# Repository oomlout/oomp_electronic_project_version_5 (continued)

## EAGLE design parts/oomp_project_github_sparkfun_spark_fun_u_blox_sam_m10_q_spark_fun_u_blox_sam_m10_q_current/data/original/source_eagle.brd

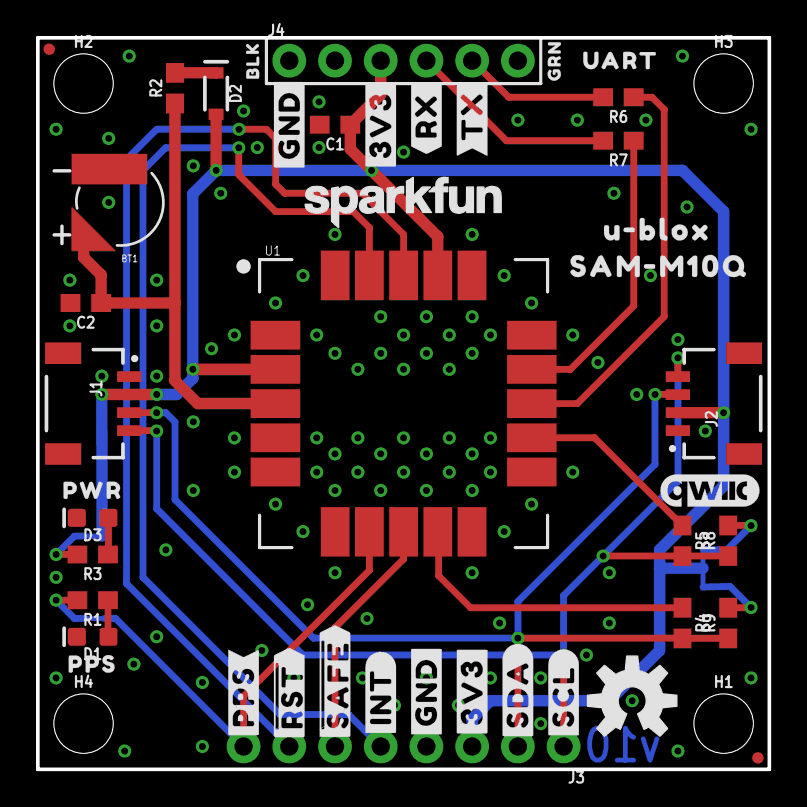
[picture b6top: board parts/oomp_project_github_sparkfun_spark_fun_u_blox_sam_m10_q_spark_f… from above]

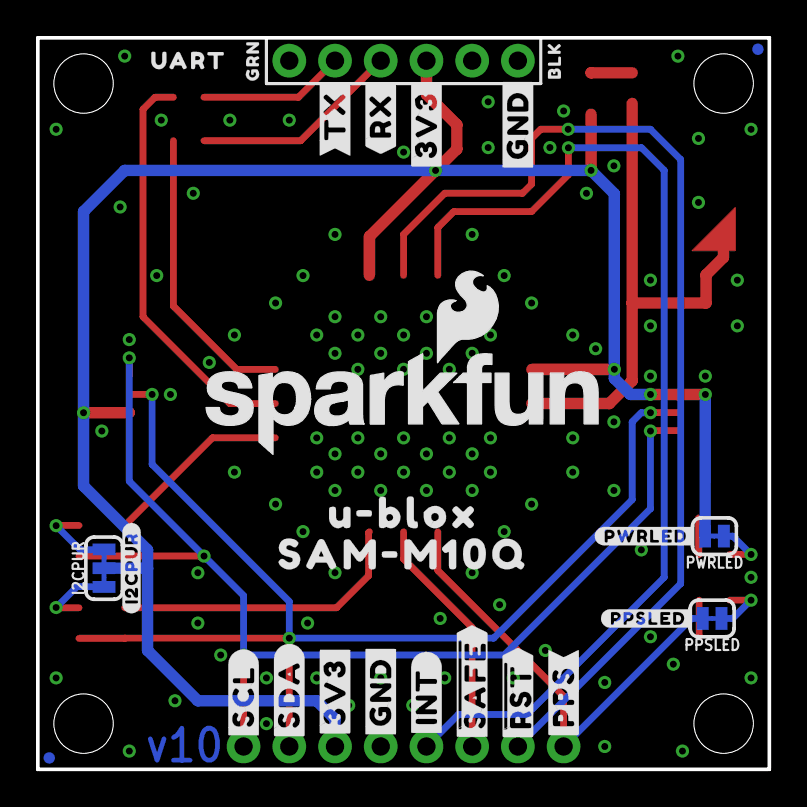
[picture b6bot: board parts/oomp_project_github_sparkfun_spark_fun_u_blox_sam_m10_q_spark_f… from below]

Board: 2 copper layers, 40.6 x 40.6 mm, 76 parts (26 on the bottom side), 22 nets.

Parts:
BT1: 6.8MM_COIN_CELL; MS421R_IV03E
C1, C2: 0.1uF; 0603
D1: Yellow; LED-0603
D2: 0.5A/40V/420mV; SOD-323
D3: RED; LED-0603
FD1, FD2, FD3, FD4: FIDUCIALUFIDUCIAL; FIDUCIAL-MICRO
FRAME1: FRAME-LETTER; CREATIVE_COMMONS
H1, H2, H3, H4: STAND-OFF
I2CPUR: JUMPER-SMT_3_2-NC_TRACE_SILK; SMT-JUMPER_3_2-NC_TRACE_SILK
J1, J2: Qwiic Right Angle; JST04_1MM_RA
J3: 1X08_NO_SILK
J4: BOOT; 1X06_NO_SILK
LOGO1: OSHW-LOGOM; OSHW-LOGO-M
LOGO2: SFE_LOGO_NAME_FLAME.2_INCH; SFE_LOGO_NAME_FLAME_.2
LOGO3: QWIIC_LOGO_CONNECTOR; QWIIC_5.5MM
PPSLED: JUMPER-SMT_2_NC_TRACE_SILK; SMT-JUMPER_2_NC_TRACE_SILK
PWRLED: JUMPER-SMT_2_NC_TRACE_SILK; SMT-JUMPER_2_NC_TRACE_SILK
R1, R8, R9: 2.2k; 0603
R2: 3.3k; 0603
R3: 1k; 0603
R4, R5: 22Ω; 0603
R6, R7: 470; 0603
U1: U-BLOX_SAM_M10Q-00B_100_PASTE; SAM-M10Q_100PASTE
U$1: SFE_LOGO_FLAME_STOP_.1
U$2: SAM#M10Q11
U$3, U$4: BLK4
U$5, U$6: GRN5
U$7, U$8: UART7
U$9: PPS9
U$10: PWR10
U$11, U$12: #TX#12
U$13, U$14: #RX#13
U$15, U$16, U$22, U$23: #3V3#0
U$17, U$20: #GND#4
U$18: U#BLOX11
U$19, U$21: #GND#5
U$24, U$25: #SCL#6
U$26, U$27: #SDA#7
U$28, U$29: #INT#8
U$30, U$33: ##RST##15
U$31: SFE_LOGO_NAME_.1
U$32: SAM#M10Q12
U$34, U$35: #PPS#13
U$36, U$37: ##SAFE##16
U$38: U#BLOX12
U$40: #PPSLED#0
U$41: #I2CPUR#0
U$42: #PWRLED#0

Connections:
3.3V: C1.1, D2.A, I2CPUR.2, J1.2, J2.2, J3.3, J4.3, PWRLED.2, U1.2, U1.17
!RESET: J3.7, U1.18
!SAFE: J3.6, U1.8
BACKUP: BT1.+, C2.1, R2.1, U1.3
GND: BT1.-, C1.2, C2.2, D1.C, D3.C, J1.1, J2.1, J3.4, J4.1, J4.2, U1.1, U1.4, U1.5, U1.6, U1.10, U1.11, U1.15, U1.16, U1.20
INT: J3.5, U1.19
unnamed: PWRLED.1, R3.2
unnamed: D1.A, R1.1
unnamed: D3.A, R3.1
unnamed: PPSLED.1, R1.2
unnamed: I2CPUR.1, R9.2
unnamed: D2.C, R2.2
unnamed: I2CPUR.3, R8.2
PPS: J3.8, PPSLED.2, U1.7
RXI: J4.4, R7.2
RXLV: R7.1, U1.14
SCL: J1.4, J2.4, J3.1, R5.2, R8.1
SCL_LV: R5.1, U1.12
SDA: J1.3, J2.3, J3.2, R4.2, R9.1
SDA_LV: R4.1, U1.9
TXLV: R6.1, U1.13
TXO: J4.5, R6.2
